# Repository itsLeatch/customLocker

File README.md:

# customLocker
This project is an electrically locked box. You can safely store things that you are addicted to inside it and unlock it by reaching a particular goal. I'm going to put sweets in it and unlock the box once I've reached my daily calorie target on my smartwatch. Inside the box is a load cell that can roughly detect the amount of sweets taken out. In addition to that, there is a wireless charger, that will charge e.g. your phone while beeing busy. 
## Why I made this project
I often find myself looking at my phone a lot when I'm busy, which slows me down. Furthermore, I also want to do more sport. With the box, I can combine these things and create my first PCB, build a large 3D model, and learn many other skills.
## Showcase
https://github.com/user-attachments/assets/28022000-88c3-4b23-8f9c-2944c17416d4

## Pictures
### 3D-Model

### PCB-Front

### PCB-Back

## Wiring
servo motor: connect the red cable to +5v
hall effect sensor: when facing the smaller side the left once is +5v, the middle one GND and the right one signal
HX711: this board is solderd directly on the PCB in the only possible direction
power: connect the 5V of the USB-C connector with the +5V on the board and the +5V on the wireless charger, same for GND
## BOM
### Aliexpress
| Description                                                                     | Link                                                                                                                                                                                                                                                       | price in USD |
|---------------------------------------------------------------------------------|------------------------------------------------------------------------------------------------------------------------------------------------------------------------------------------------------------------------------------------------------------|--------------|
| ESP32-32D to control everything                                                 | https://de.aliexpress.com/item/4000093185394.html?spm=a2g0o.cart.0.0.b1964ae4QiPiLO&mp=1&gatewayAdapt=glo2deu                                                                                                                                              |         3,56 |
| load cell (5KG AND HX711) to detect the amount of removed items                 | https://de.aliexpress.com/item/4001274733879.html?spm=a2g0o.cart.0.0.b1964ae4QiPiLO&mp=1&gatewayAdapt=glo2deu                                                                                                                                              |          1,9 |
| 0.96 inch display (white) to display information such as left time, calorien... | https://de.aliexpress.com/item/1005006141235306.html?spm=a2g0o.cart.0.0.b1964ae4QiPiLO&mp=1&gatewayAdapt=glo2deu                                                                                                                                           |         1,97 |
| servo motor (360°) to lock/open the box                                         | https://de.aliexpress.com/item/1005007173214082.html?spm=a2g0o.cart.0.0.b1964ae4QiPiLO&mp=1&gatewayAdapt=glo2deu                                                                                                                                           |          1,8 |
| passive buzzer to notify the user                                               | https://de.aliexpress.com/item/1005008825917787.html?spm=a2g0o.cart.0.0.b1964ae4QiPiLO&mp=1&gatewayAdapt=glo2deu                                                                                                                                           |         1,86 |
| keys (blue) for user inputs                                                     | https://de.aliexpress.com/item/1005004341695529.html?spm=a2g0o.cart.0.0.b1964ae4QiPiLO&mp=1&gatewayAdapt=glo2deu                                                                                                                                           |         1,62 |
| key caps (red) for the keys                                                     | https://de.aliexpress.com/item/1005007209930123.html?spm=a2g0o.cart.0.0.64164ae4YkwdOF&mp=1&gatewayAdapt=glo2deu                                                                                                                                           |         7,26 |
| wireless charger (b) if the smartphone or simular is in the box                 | https://de.aliexpress.com/item/1005006386722006.html?spm=a2g0o.cart.0.0.64164ae4YkwdOF&mp=1&gatewayAdapt=glo2deu                                                                                                                                           |         5,76 |
| hall effect sensor (47E) to check if the box is open or closed                  | https://de.aliexpress.com/item/1005008647103022.html?spm=a2g0o.cart.0.0.64164ae4YkwdOF&mp=1&gatewayAdapt=glo2deu                                                                                                                                           |          1,8 |
| magnetic tape (10mmx1mm, 1 Meter) for the hall effect sensor                    | https://de.aliexpress.com/item/1005006757451588.html?spm=a2g0o.cart.0.0.64164ae4YkwdOF&mp=1&gatewayAdapt=glo2deu                                                                                                                                           |         2,39 |
| USB-C PCB for power                                                             | https://de.aliexpress.com/item/1005009193894473.html?spm=a2g0o.cart.0.0.64164ae4YkwdOF&mp=1&gatewayAdapt=glo2deu                                                                                                                                           |         1,15 |
| connector pins (each color) to connect the components to the PCB                | https://de.aliexpress.com/item/1005007324368709.html?spm=a2g0o.cart.0.0.64164ae4YkwdOF&mp=1&gatewayAdapt=glo2deu                                                                                                                                           |         1,36 |
| some cables (M-F-20pin) to connect the components as well                       | https://de.aliexpress.com/item/1005007805542492.html?spm=a2g0o.cart.0.0.64164ae4YkwdOF&mp=1&gatewayAdapt=glo2deu                                                                                                                                           |         1,24 |
| M4x16mm screws to mount most of the components                                  | https://de.aliexpress.com/item/1005006674812661.html?spm=a2g0o.cart.0.0.64164ae4YkwdOF&mp=1&gatewayAdapt=glo2deu                                                                                                                                           |         1,77 |
| m4 threaded inserts (OD 6mm, lenght 6mm) for the screws                         | https://de.aliexpress.com/item/1005003582355741.html?spm=a2g0o.cart.0.0.64164ae4YkwdOF&mp=1&gatewayAdapt=glo2deu                                                                                                                                           |         2,59 |
| M5x30 screws to mount the load cell and the opening mechanism of the box        | https://de.aliexpress.com/item/1005006051322108.html?spm=a2g0o.productlist.main.35.1d807847E9uYf0&algo_pvid=ca520a57-ad42-44bf-a79a-73b8be690855&pdp_ext_f=%7B%22order%22%3A%22272%22%2C%22eval%22%3A%221%22%7D&utparam-url=scene%3Asearch%7Cquery_from%3A |         3,26 |
| shipping cost to Germany                                                        |                                                                                                                                                                                                                                                            |         6,27 |
| total price for ALIEXPRESS                                                      |                                                                                                                                                                                                                                                            |        47,56 |
### local building center
| Description                                                                                                                             | price in €  |
|-----------------------------------------------------------------------------------------------------------------------------------------|-------------|
| 2 pices M4 DIN9021 to spread the pressure over the box                                                                                  | 2X0,24=0,48 |
| 2 pices M5 DIN9021 to spread the pressure over the box                                                                                  | 2x0,29=0,58 |
| 2 pieces M5 domed cap nut                                                                                                               | 2x0,49=0,98 |
| total price in €                                                                                                                        | 2,04€       |
| total price in $ (7/17/2025 at 4:44pm under: https://www.visa.de/support/verbraucher/visa-reiseservices/exchange-rate-calculator.html)  | 2,39$       |

### PCB from jlcpcp
| Description                                            | price in $ |
|--------------------------------------------------------|------------|
| 2 pices M4 DIN9021 to spread the pressure over the box |          4 |
| shipping cost                                          |        3,3 |
| total                                                  |        7,3 |

### total cost
| Description           | price in $                                                                 |
|-----------------------|----------------------------------------------------------------------------|
| aliexpress            |                                                                      47,56 |
| local building center |                                                                       2,39 |
| PCB                   |                                                                        7,3 |
| 3D-Filament           | nothing - I have to use Printing Legion because I have no 3D-Printer yet 😥 |
| total                 |                                                                      **57,25** |

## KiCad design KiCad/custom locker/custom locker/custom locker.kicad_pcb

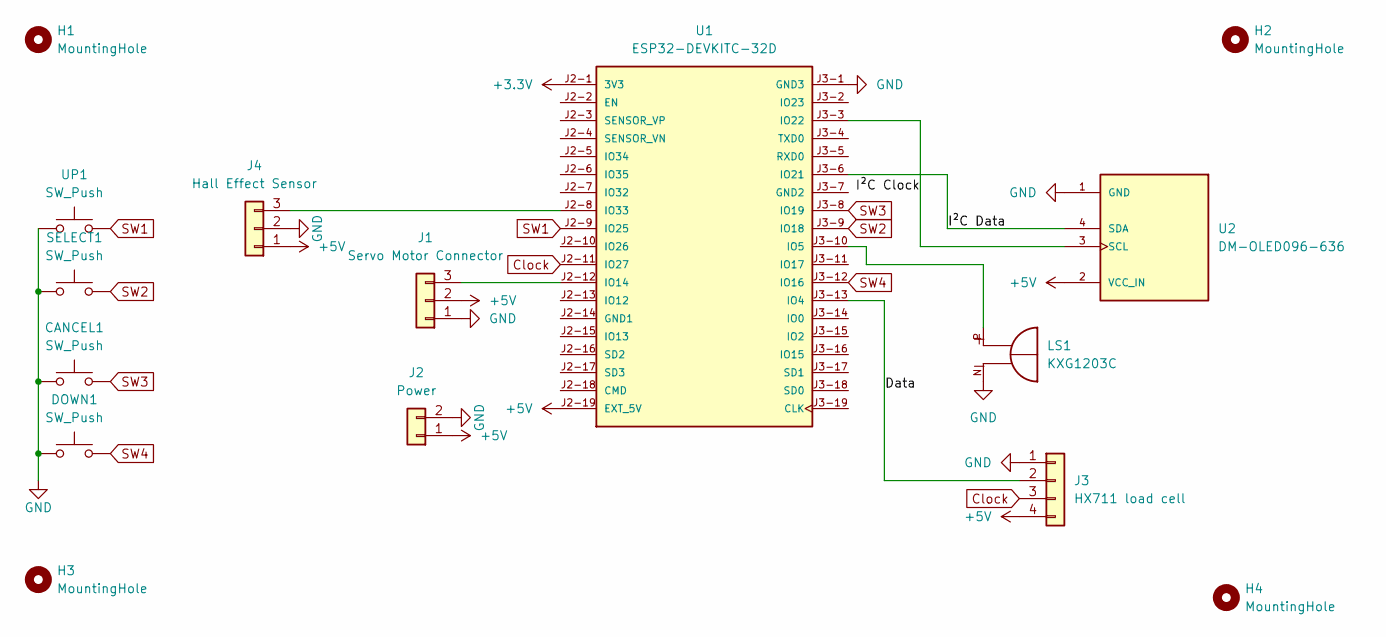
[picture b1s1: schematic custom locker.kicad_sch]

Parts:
CANCEL1: SW_Push; SW_Cherry_MX_1.00u_PCB
DOWN1: SW_Push; SW_Cherry_MX_1.00u_PCB
H1, H2, H3, H4: MountingHole; MountingHole_4.3mm_M4
J1: Servo Motor Connector; PinHeader_1x03_P2.54mm_Vertical
J2: Power; PinHeader_1x02_P2.54mm_Vertical
J3: HX711 load cell; PinHeader_1x04_P2.54mm_Vertical
J4: Hall Effect Sensor; PinHeader_1x03_P2.54mm_Vertical
LS1: KXG1203C; XDCR_KXG1203C; PARTREV 1.3
SELECT1: SW_Push; SW_Cherry_MX_1.00u_PCB
U1: ESP32-DEVKITC-32D; MODULE_ESP32-DEVKITC-32D; PARTREV V4
U2: DM-OLED096-636; MODULE_DM-OLED096-636; PARTREV 2018-09-10
UP1: SW_Push; SW_Cherry_MX_1.00u_PCB

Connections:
+3.3V: U1.J2-1 (3V3)
+5V: J1.2, J2.1, J3.4, J4.1, U1.J2-19 (EXT_5V), U2.2 (VCC_IN)
/Data: J3.2, U1.J3-13 (IO4)
/I²C Clock: U1.J3-3 (IO22), U2.3 (SCL)
/I²C Data: U1.J3-6 (IO21), U2.4 (SDA)
Clock: J3.3, U1.J2-11 (IO27)
GND: CANCEL1.1, DOWN1.1, J1.1, J2.2, J3.1, J4.2, LS1.N, SELECT1.1, U1.J3-1 (GND3), U2.1 (GND), UP1.1
unnamed: J1.3, U1.J2-12 (IO14)
unnamed: J4.3, U1.J2-8 (IO33)
unnamed: LS1.P, U1.J3-10 (IO5)
SW1: U1.J2-9 (IO25), UP1.2
SW2: SELECT1.2, U1.J3-9 (IO18)
SW3: CANCEL1.2, U1.J3-8 (IO19)
SW4: DOWN1.2, U1.J3-12 (IO16)

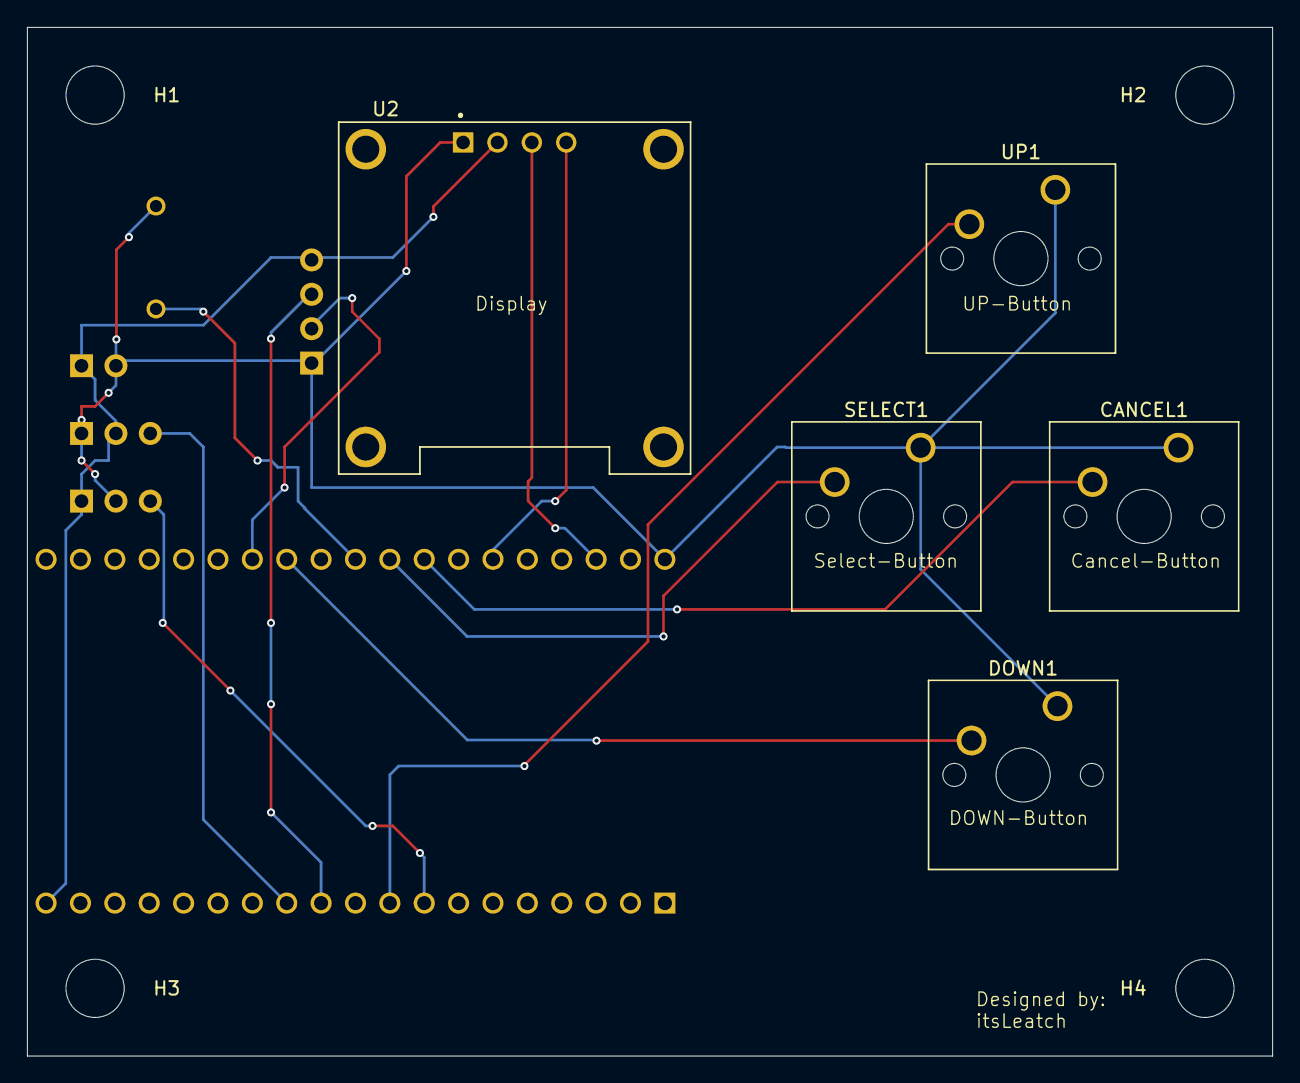
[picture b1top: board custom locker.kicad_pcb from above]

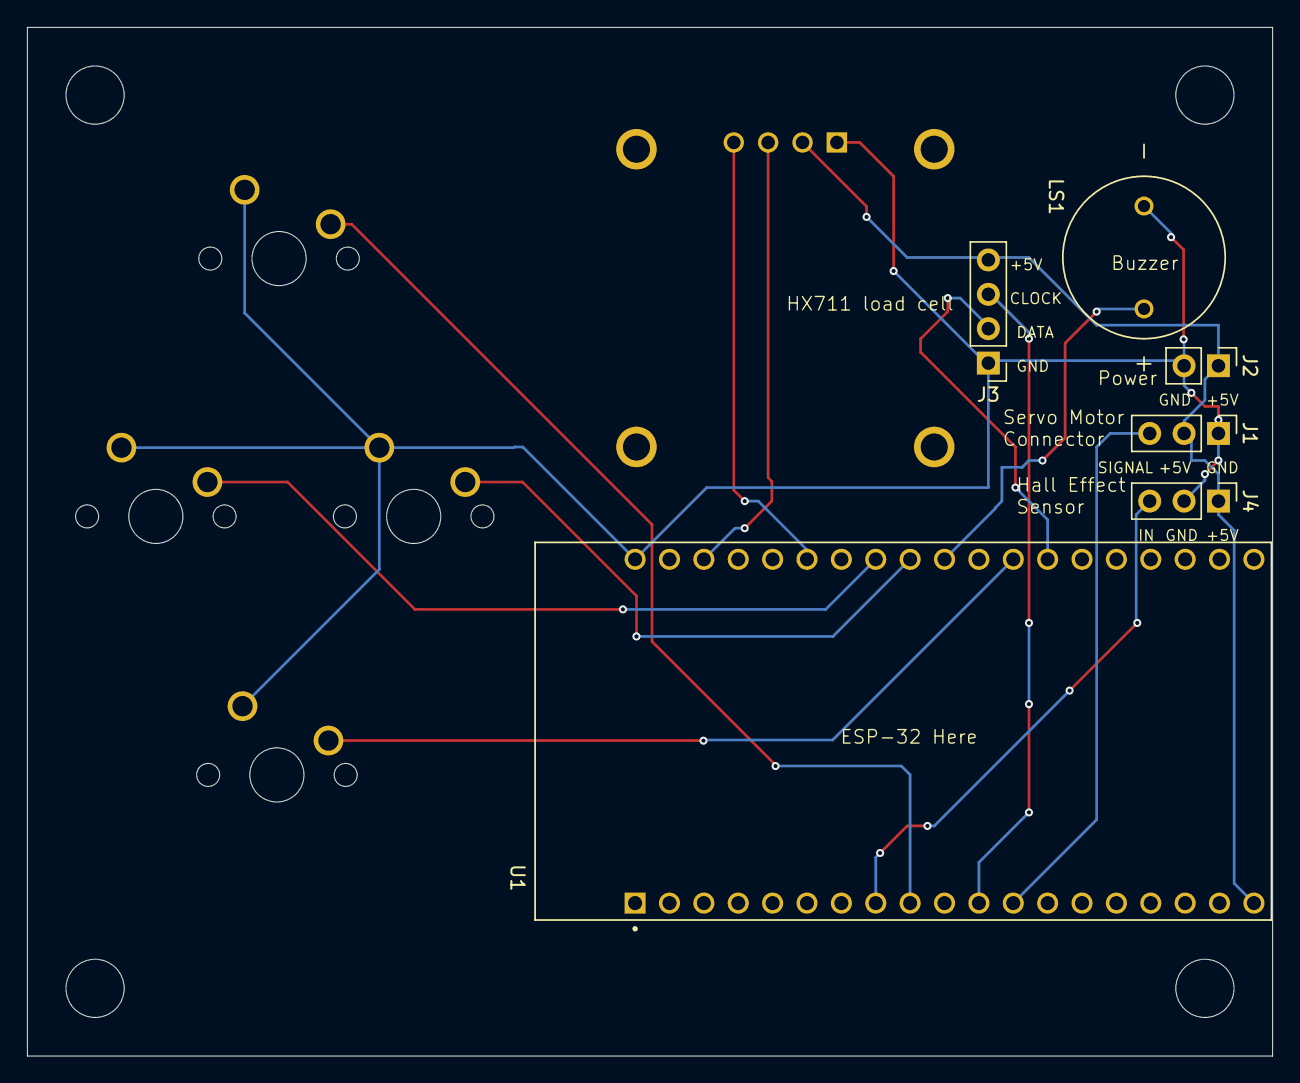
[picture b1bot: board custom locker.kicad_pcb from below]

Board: 2 copper layers, 92.0 x 76.0 mm, 15 parts (6 on the bottom side), 13 nets.

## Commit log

2025-06-09 fulfill the guidlines
2025-06-12 Day 2 update
2025-06-26 add KiCad Project for Day3
2025-06-26 Update JOURNAL.md for Day 3
2025-07-01 finished pcb
2025-07-01 PCB wiring
2025-07-01 little changes on PCB
    mainly added screw holes
2025-07-01 Update JOURNAL.md (day 4)
2025-07-02 Update JOURNAL.md (day 5)
2025-07-03 Update JOURNAL.md (day 6)
2025-07-06 small PCB changes
2025-07-06 Update JOURNAL.md (day 7)
2025-07-06 Update JOURNAL.md (day 8)
2025-07-06 added all the files
2025-07-17 final submission files
2025-07-17 Update README.md for submission
2025-07-17 small improvments and the bom as csv
2025-07-17 Update JOURNAL.md (day 9)
2025-07-30 Added the firmware
2026-04-29 Add showcase section to README
    Added a showcase section with a link to project assets.
